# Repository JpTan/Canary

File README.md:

# Canary
A sensor network of compact indoor air quality monitors

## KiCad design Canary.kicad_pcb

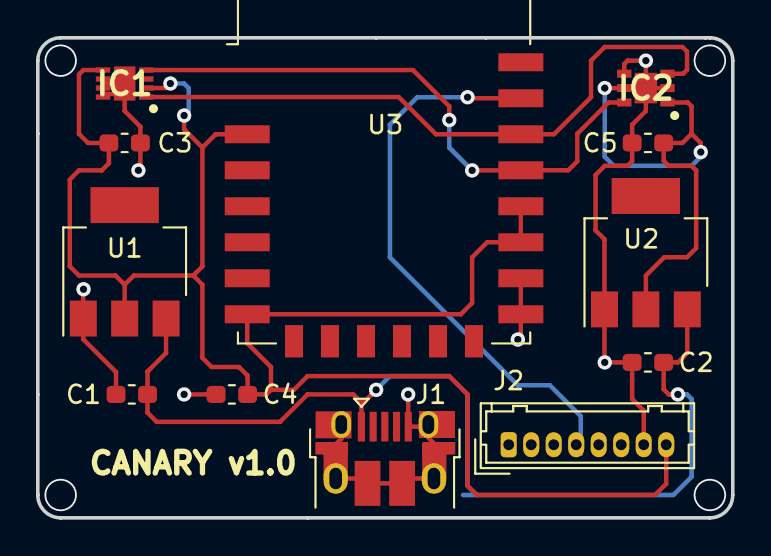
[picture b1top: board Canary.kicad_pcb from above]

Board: 2 copper layers, 38.6 x 26.7 mm, 12 parts (0 on the bottom side), 8 nets.

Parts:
C1, C2, C3, C4, C5: 100nF; C_0603_1608Metric_Pad1.05x0.95mm_HandSolder
IC1: SHT30-DIS-B; SON50P250X250X100-9N
IC2: SGP30-2.5k; SON80P245X245X90-7N
J1: USB_B_Micro; USB_Micro-B_Amphenol_10103594-0001LF_Horizontal
J2: PMS5003; Hirose_DF13-08P-1.25DSA_1x08_P1.25mm_Vertical
U1: AMS1117-3.3; SOT-223
U2: AMS1117-1.8; SOT-223
U3: ESP-12F; ESP-12E

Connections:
1.8V: C5.1, IC2.1, IC2.5, U2.2
GND: C1.2, C2.2, C3.2, C4.2, C5.2, IC1.6, IC1.7, IC1.8, IC1.9, IC2.2, IC2.4, IC2.7, J1.5, J1.6, J2.7, U1.1, U2.1, U3.15, U3.16
N.C.: J2.1, J2.2
unnamed: C1.1, C2.1, J1.1, U1.3, U2.3
SCK: IC1.4, IC2.6, U3.19
SDA: IC1.1, IC2.3, U3.20
TXD: J2.4, U3.21
VCC: C3.1, C4.1, IC1.2, IC1.5, J2.8, U1.2, U3.3, U3.8, U3.17, U3.18

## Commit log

2019-08-28 Version 1.0 design
